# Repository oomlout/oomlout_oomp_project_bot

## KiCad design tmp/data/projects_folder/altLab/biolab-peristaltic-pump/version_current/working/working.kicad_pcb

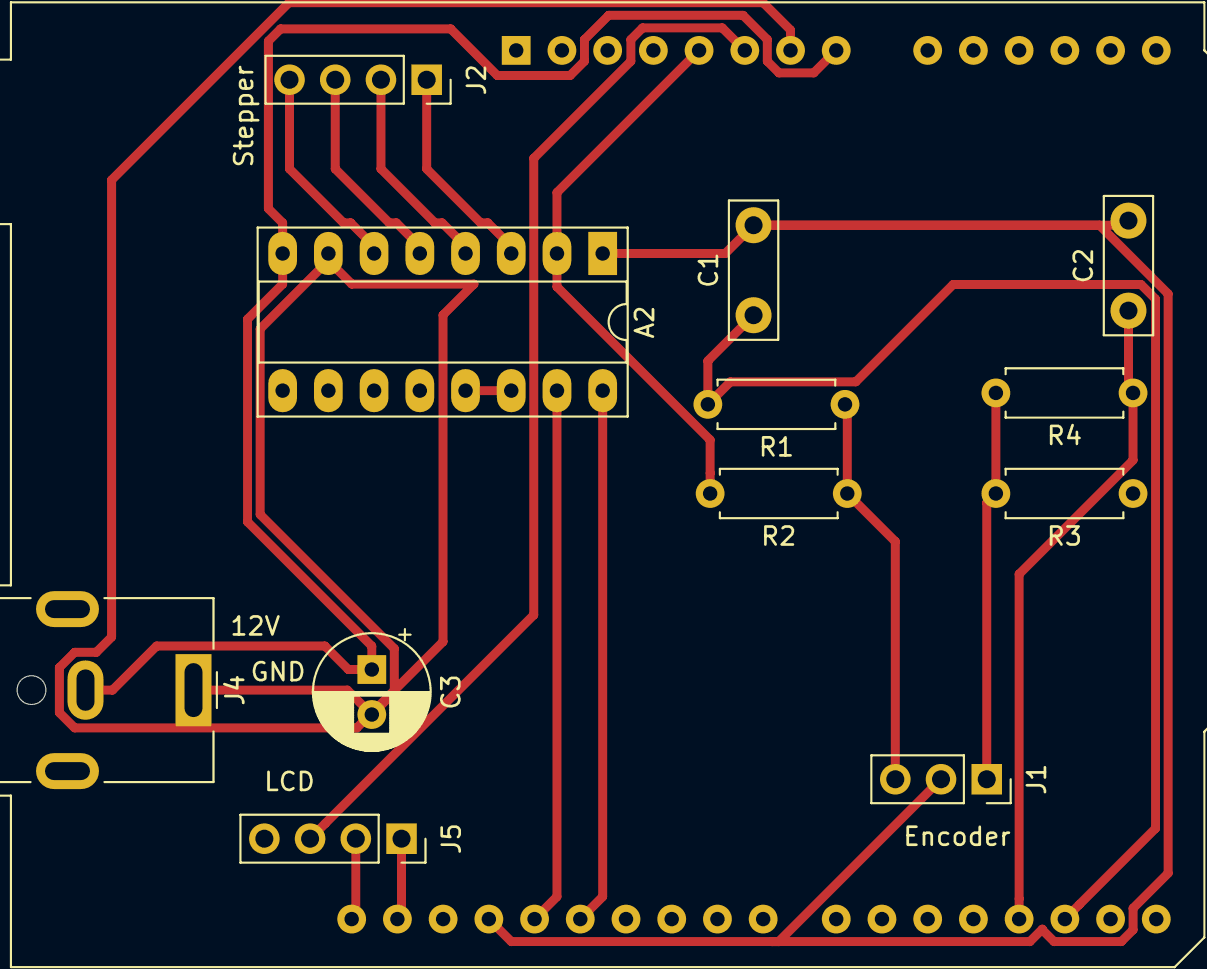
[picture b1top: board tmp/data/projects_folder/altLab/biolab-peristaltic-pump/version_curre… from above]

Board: 2 copper layers, 13 parts (0 on the bottom side), 18 nets.

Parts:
A1: Arduino_UNO_R3
A2: Pololu_Breakout_A4988; DIP-16_W7.62mm_Socket_LongPads
C1, C2: CP; C_Disc_D7.5mm_W2.5mm_P5.00mm
C3: C; CP_Radial_D6.3mm_P2.50mm
J1: Encoder; PinSocket_1x03_P2.54mm_Vertical
J2: Stepper; PinSocket_1x04_P2.54mm_Vertical
J4: Power12V; BarrelJack_CUI_PJ-063AH_Horizontal
J5: LCD-I2C; PinSocket_1x04_P2.54mm_Vertical
R1, R2, R3, R4: R; R_Axial_DIN0207_L6.3mm_D2.5mm_P7.62mm_Horizontal

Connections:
unnamed: A1.5, A2.2, R2.2, R3.1
unnamed: A1.6, J5.3
unnamed: A1.7, A2.7, C3.2, J4.1
unnamed: A1.8, A2.8, C3.1, J4.2
unnamed: A1.17, C1.1, R1.2
unnamed: A1.18, C2.1, R4.1
unnamed: A1.27, A2.16
unnamed: A1.28, A2.15
unnamed: A1.29, A2.1, C1.2, C2.2, J1.2
unnamed: A1.31, J5.1
unnamed: A1.32, J5.2
unnamed: A2.3, J2.1
unnamed: A2.4, J2.2
unnamed: A2.5, J2.3
unnamed: A2.6, J2.4
unnamed: A2.13, A2.14
unnamed: J1.1, R3.2, R4.2
unnamed: J1.3, R1.1, R2.1

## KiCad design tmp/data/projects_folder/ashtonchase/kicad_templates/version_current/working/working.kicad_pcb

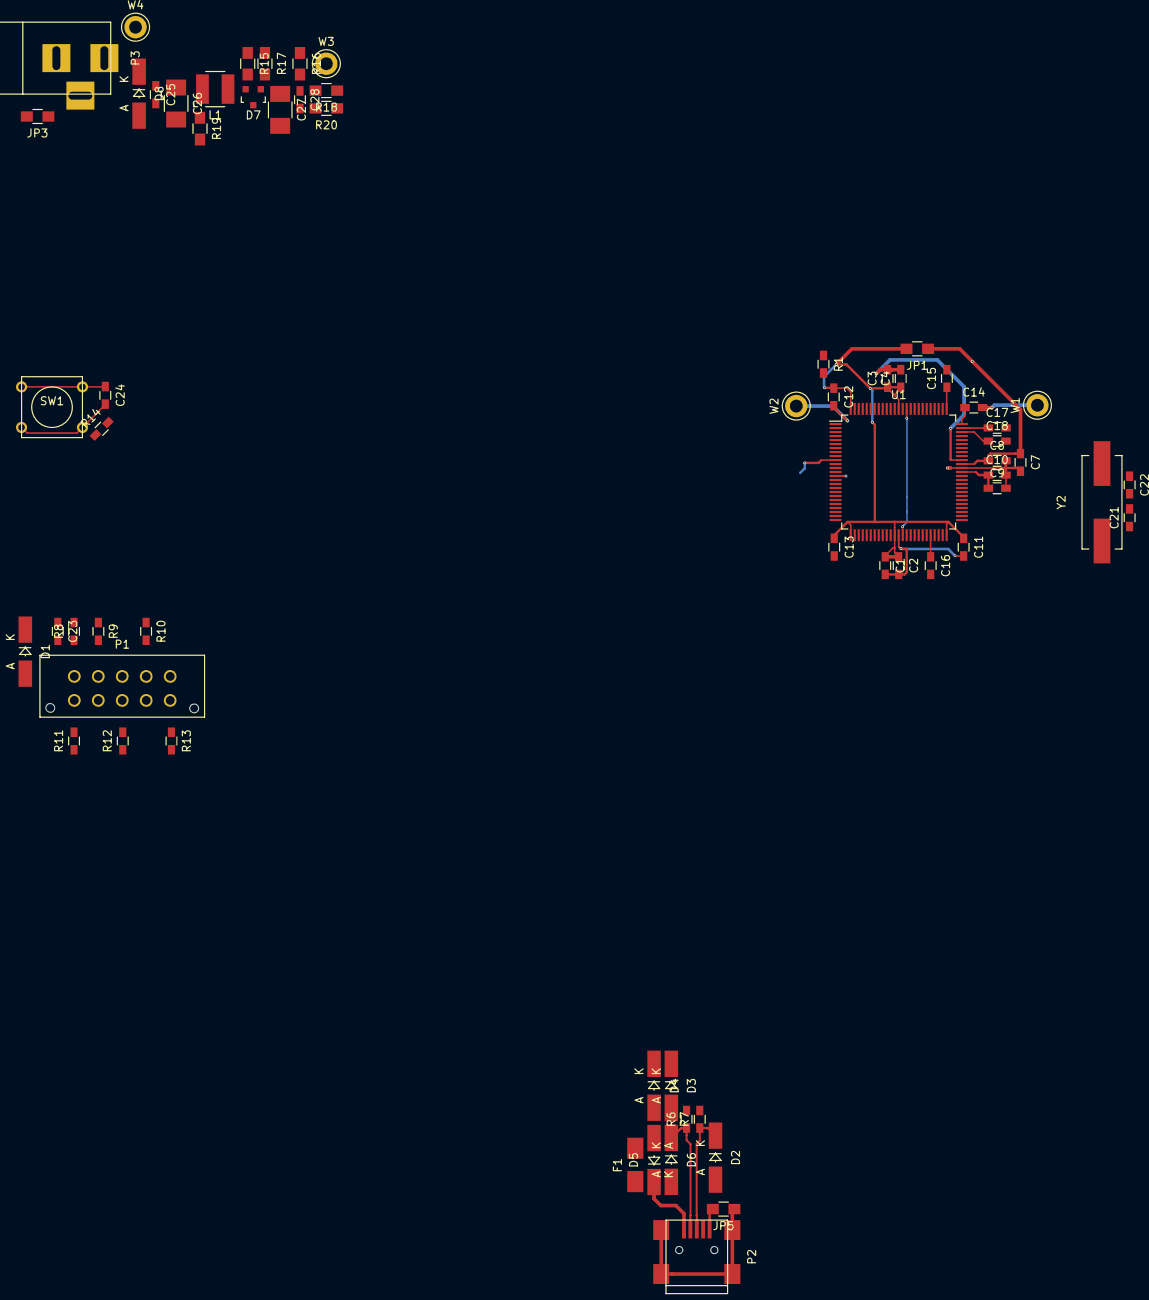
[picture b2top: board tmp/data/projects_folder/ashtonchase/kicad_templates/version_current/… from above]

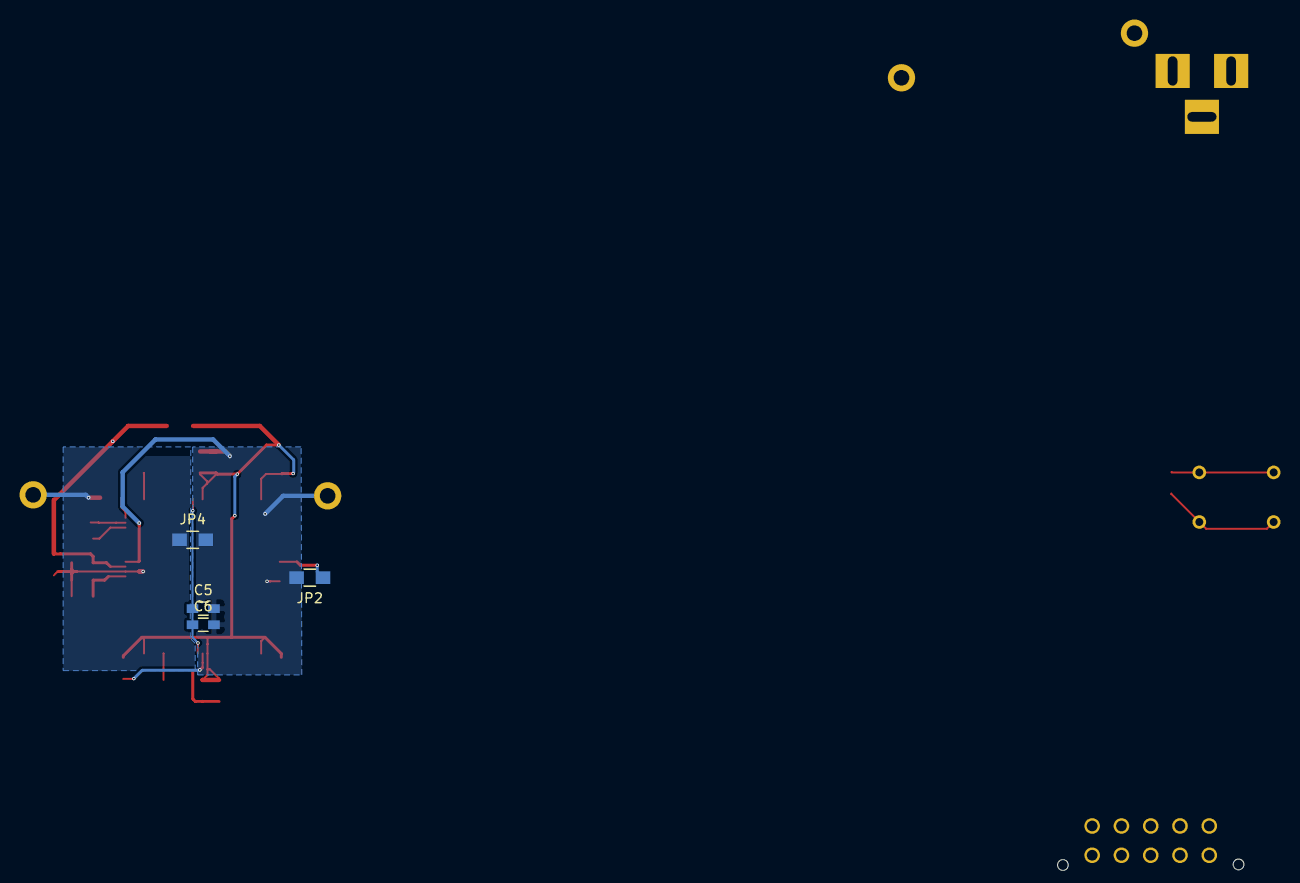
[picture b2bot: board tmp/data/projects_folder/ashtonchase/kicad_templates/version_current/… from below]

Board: 2 copper layers, 67 parts (4 on the bottom side), 39 nets.

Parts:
C1, C3, C5, C7, C9, C15, C16, C17, C18: 1.0UF; R_0603_HandSoldering
C2, C4, C6, C8, C10, C11, C12, C13, C14, C23, C24, C25, C28: 0.1UF; R_0603_HandSoldering
C21, C22: 22PF; R_0603_HandSoldering
C26, C27: 22UF; R_1210_HandSoldering
D1, D2, D5, D6: TVS; MiniMELF_Handsoldering
D3, D4: D_Schottky; MiniMELF_Handsoldering
D7: ZHCS; SOT-23
D8: D; MiniMELF_Handsoldering
F1: FUSE; Fuse_SMD1206_HandSoldering
JP1, JP2, JP3, JP4, JP5: Jumper_NC_Small; R_0805_HandSoldering
L1: 22UH; NR4018
P1: CONN_02X05; Molex_Microfit3_Header_02x05_Straight_43045-1028
P2: USB_OTG; USB_Mini-B
P3: CONN_01X02; BARREL_JACK
R1: 0; R_0603_HandSoldering
R6, R7: 22; R_0603_HandSoldering
R8, R9, R10, R11, R12, R13: 10; R_0603_HandSoldering
R14: 4.7K; R_0603_HandSoldering
R15, R16, R17, R19, R20: NL; R_0805_HandSoldering
R18: 0; R_0805_HandSoldering
SW1: SW_PUSH; SW_PUSH_SMALL
U1: CY8C5888AXI-LP096; LQFP-100_14x14mm_Pitch0.5mm
W1, W2, W3, W4: TEST_1P; Test_Point_Keystone_5010-5014_Multipurpose
Y2: 32.768KHZ; Crystal_HC49-SD_SMD

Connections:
/MCU/P0.2: C18.1, U1.73
/MCU/P0.3: C17.1, U1.74
/MCU/P0.4: C15.1, U1.76
/MCU/P3.2: C16.1, U1.46
/MCU/RTC_N: C22.1, U1.56, Y2.2
/MCU/RTC_P: C21.1, U1.55, Y2.1
/MCU/USBP_N: R6.2, U1.36
/MCU/USBP_P: R7.2, U1.35
/MCU/VCCA: C9.1, C10.1, U1.63
/MCU/VCCD: C5.1, C6.1, U1.39, U1.86
/PSoC Extra Circuits/USB_VCC: D5.1, F1.1, P2.1
Earth: JP5.1, P2.6
GNDA: C7.2, C8.2, C9.2, C10.2, C14.2, C15.2, C16.2, C17.2, C18.2, C21.2, C22.2, JP4.1, U1.64, W1.1
GNDD: C1.2, C2.2, C3.2, C4.2, C5.2, C6.2, C11.2, C12.2, C13.2, C23.2, C24.2, D1.2, D2.2, D5.2, D6.2, JP2.2, JP3.2, JP4.2, JP5.2, P1.3, P1.5, P1.7, P1.9, P2.5, SW1.2, U1.14, U1.38, U1.66, U1.87, W2.1
GNDPWR: JP2.1, U1.10
IND: R15.1, U1.11
unnamed: C27.1, C28.1, D7.1, R16.2, R17.2, R18.2
unnamed: D3.2, D4.2, F1.2
unnamed: D7.2, L1.2, R15.2
unnamed: P1.1, R8.1
unnamed: P1.2, R9.2
unnamed: P1.4, R10.2
unnamed: P1.6, R11.2
unnamed: P1.8, R12.2
unnamed: P1.10, R13.2
P1.0_TMS: R9.1, U1.20
P1.1_TCK: R10.1, U1.21
P1.4_TDO: R11.1, U1.24
P1.5_TDI: R12.1, U1.25
P1.6_nRST: R13.1, U1.27
USB_N: D6.1, P2.2, R6.1
USB_P: D2.1, P2.3, R7.1
VBATT: C25.1, C26.1, D8.1, L1.1, P3.1, R19.1, U1.13, W4.1
VBATT_GND: C25.2, C26.2, C27.2, C28.2, D8.2, JP3.1, P3.2, R19.2, R20.2
VBOOST: R18.1, R20.1, U1.12, W3.1
VDDA: C7.1, C8.1, C14.1, D4.1, JP1.1, R17.1, U1.65, U1.75
VDDD: C1.1, C2.1, C3.1, C4.1, C11.1, C12.1, C13.1, D3.1, JP1.2, R1.1, R16.1, U1.26, U1.37, U1.50, U1.88, U1.100
VTARG: C23.1, D1.1, R1.2, R8.2, R14.1
XRES: C24.1, R14.2, SW1.1, U1.15

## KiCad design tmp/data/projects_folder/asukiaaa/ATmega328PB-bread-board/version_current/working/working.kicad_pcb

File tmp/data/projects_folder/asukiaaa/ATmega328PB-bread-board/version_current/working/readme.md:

# ATmega328PB-bread-board by asukiaaa  
This is a harvested standardized copy of a project from github.  
The original project can be found at:  
https://github.com/asukiaaa/ATmega328PB-bread-board  
Please consult that link for additional, details, files, and license information.  
Note: It was auto harvested and if the original repo had more than one board file or anything out of the ordinary the files here are likely not representative.

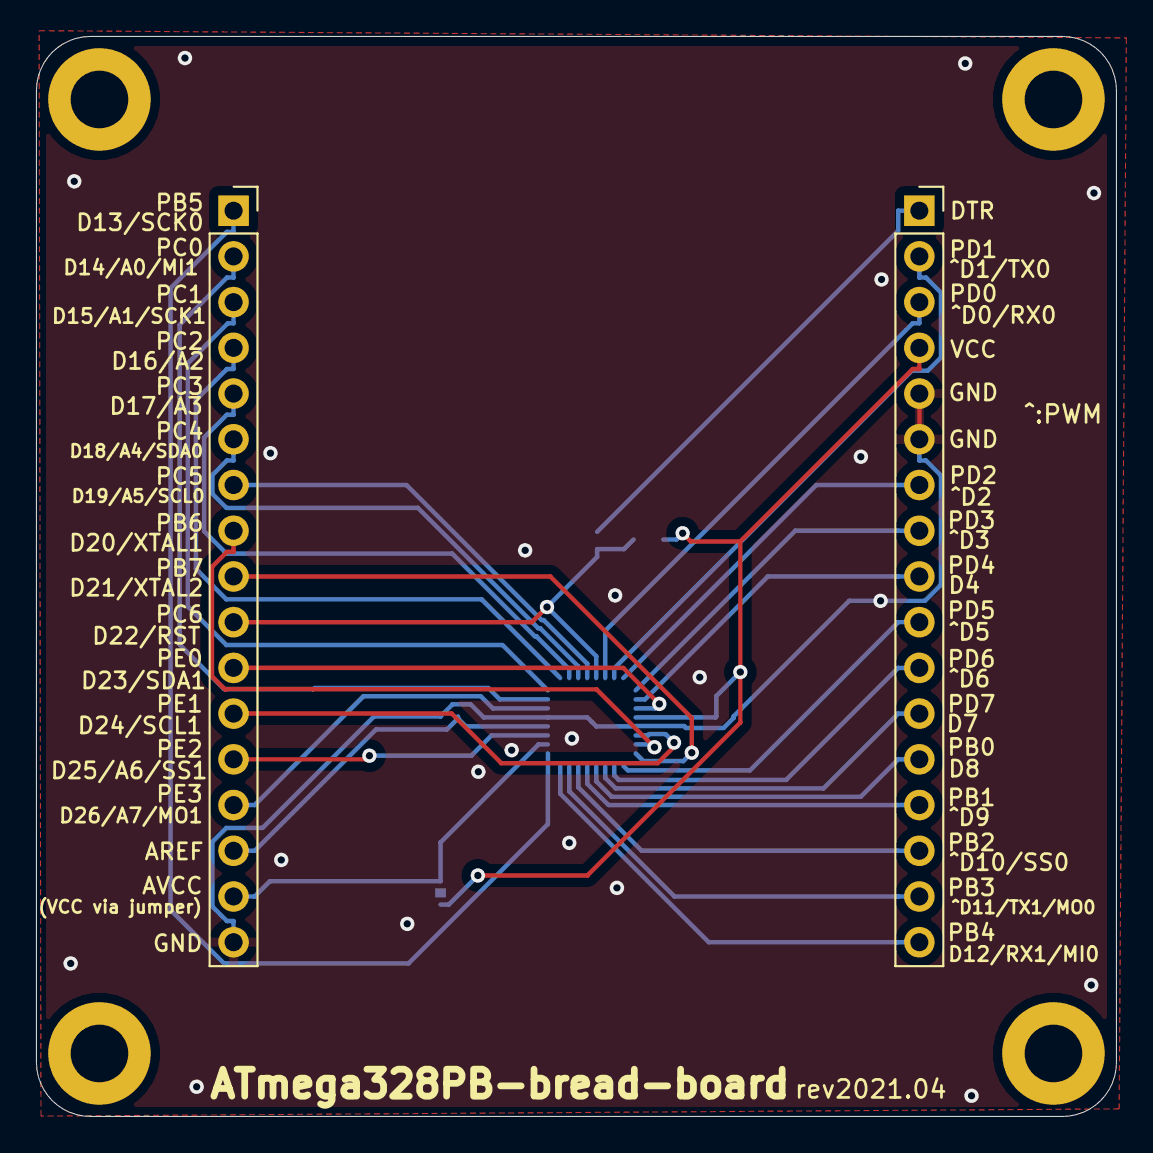
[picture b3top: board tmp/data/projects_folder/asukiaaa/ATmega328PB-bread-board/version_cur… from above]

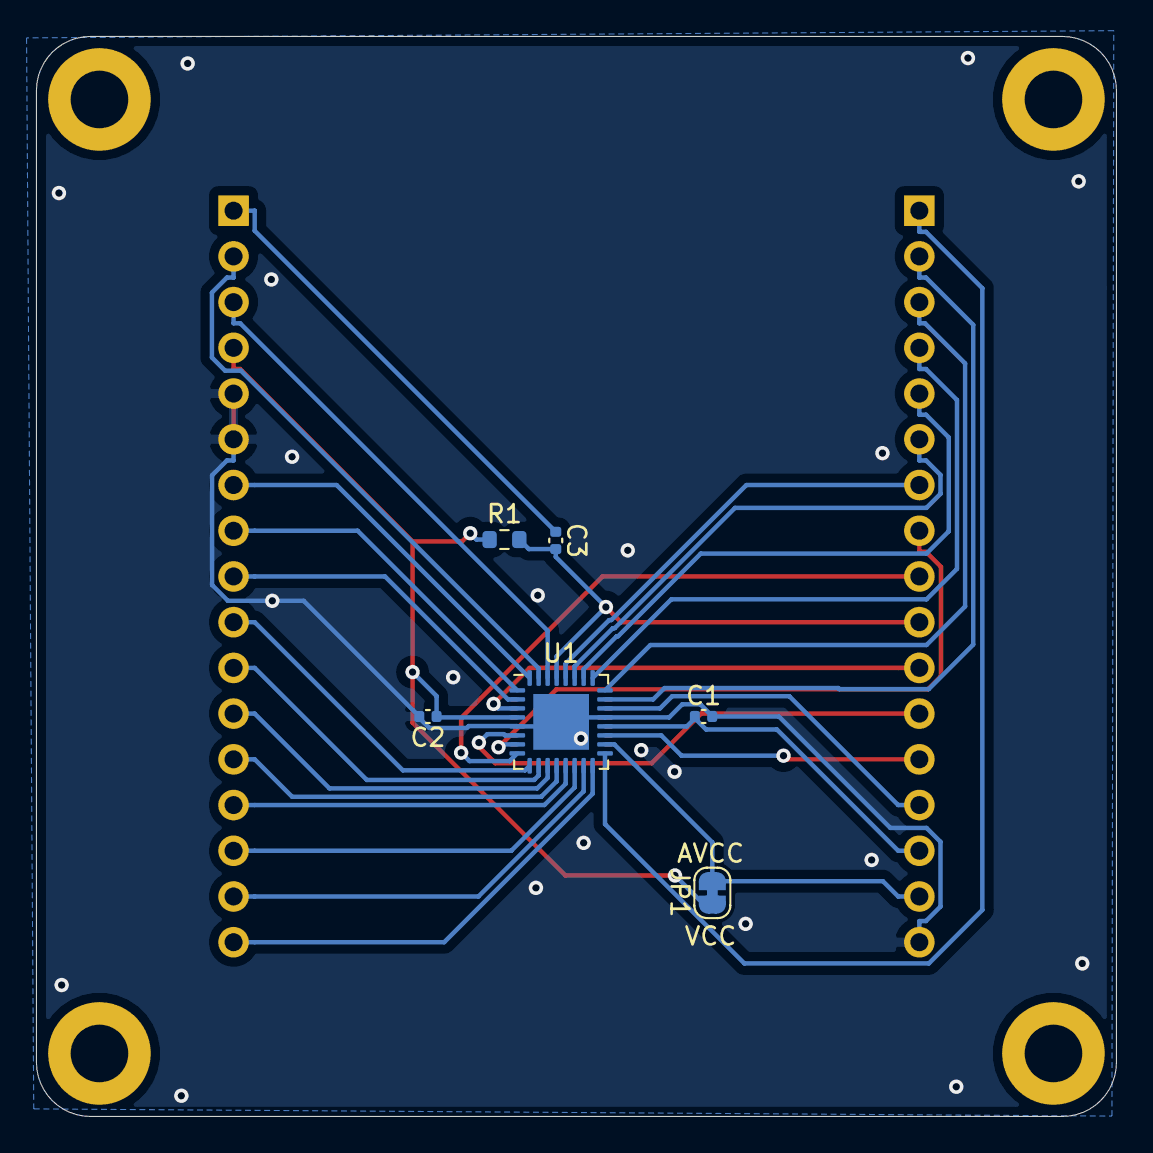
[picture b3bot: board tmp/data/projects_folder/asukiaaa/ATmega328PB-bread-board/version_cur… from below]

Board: 2 copper layers, 60.0 x 60.0 mm, 12 parts (6 on the bottom side), 32 nets.

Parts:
C1, C2, C3: 0.1uf; C_0402_1005Metric
J1, J2: Conn_01x17; PinSocket_1x17_P2.54mm_Vertical
JP1: NC; SolderJumper-2_P1.3mm_Bridged_RoundedPad1.0x1.5mm
R1: 10k; R_0603_1608Metric
REF1, REF2, REF3, REF4: MountingHole_3.2mm_M3_ISO7380_Pad
U1: ATmega328PB-MU; QFN-32-1EP_5x5mm_P0.5mm_EP3.1x3.1mm

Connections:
/DTR: C3.1, J1.1
/aref: C1.1, J2.15, U1.20
/avcc: J2.16, JP1.2, U1.18
/pb0: J1.13, U1.12
/pb1: J1.14, U1.13
/pb2: J1.15, U1.14
/pb3: J1.16, U1.15
/pb4: J1.17, U1.16
/pb5: J2.1, U1.17
/pb6: J2.8, U1.7
/pb7: J2.9, U1.8
/pc0: J2.2, U1.23
/pc1: J2.3, U1.24
/pc2: J2.4, U1.25
/pc3: J2.5, U1.26
/pc4: J2.6, U1.27
/pc5: J2.7, U1.28
/pc6: C3.2, J2.10, R1.2, U1.29
/pd0: J1.3, U1.30
/pd1: J1.2, U1.31
/pd2: J1.7, U1.32
/pd3: J1.8, U1.1
/pd4: J1.9, U1.2
/pd5: J1.10, U1.9
/pd6: J1.11, U1.10
/pd7: J1.12, U1.11
/pe0: J2.11, U1.3
/pe1: J2.12, U1.6
/pe2: J2.13, U1.19
/pe3: J2.14, U1.22
GND: C1.2, C2.2, J1.5, J1.6, J2.17, U1.5, U1.21, U1.33
VCC: C2.1, J1.4, JP1.1, R1.1, U1.4

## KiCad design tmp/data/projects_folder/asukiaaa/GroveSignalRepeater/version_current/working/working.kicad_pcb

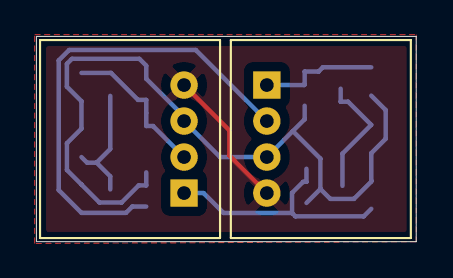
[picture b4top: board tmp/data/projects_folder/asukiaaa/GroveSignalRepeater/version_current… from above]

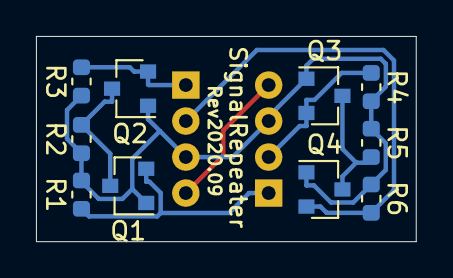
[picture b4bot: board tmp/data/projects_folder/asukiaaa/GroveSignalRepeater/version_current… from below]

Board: 2 copper layers, 21.1 x 11.4 mm, 12 parts (10 on the bottom side), 8 nets.

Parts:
J1, J2: Conn_01x04; NS-Tech_Grove_1x04_P2mm_Horizontal
Q1, Q2, Q3, Q4: Q_NMOS_GSD; SOT-23
R1, R2, R3, R4, R5, R6: 10k; R_0603_1608Metric

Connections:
/CON1_A: J1.1, Q1.2, R1.1
/CON1_B: J1.2, Q3.2, R4.1
/CON2_A: J2.1, Q2.2, R3.2
/CON2_B: J2.2, Q4.2, R6.2
GND: J1.4, J2.4
unnamed: Q1.3, Q2.3, R2.2
unnamed: Q3.3, Q4.3, R5.2
VCC: J1.3, J2.3, Q1.1, Q2.1, Q3.1, Q4.1, R1.2, R2.1, R3.1, R4.2, R5.1, R6.1

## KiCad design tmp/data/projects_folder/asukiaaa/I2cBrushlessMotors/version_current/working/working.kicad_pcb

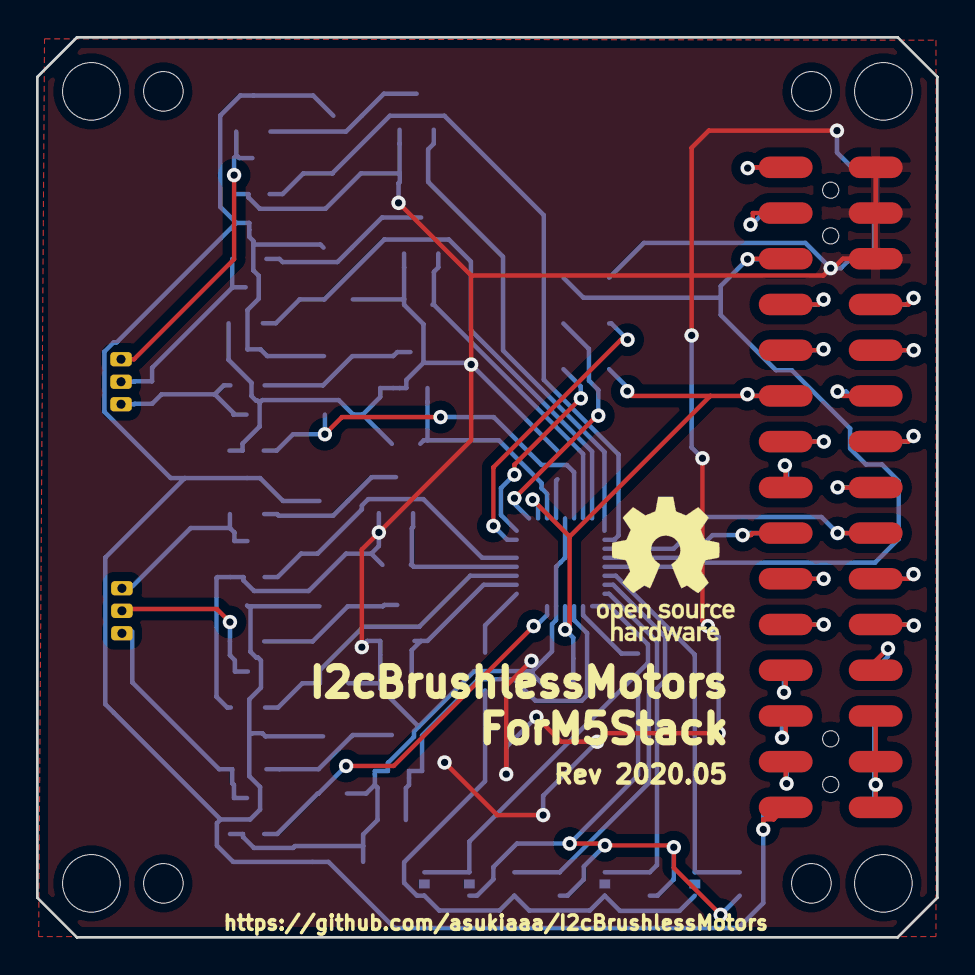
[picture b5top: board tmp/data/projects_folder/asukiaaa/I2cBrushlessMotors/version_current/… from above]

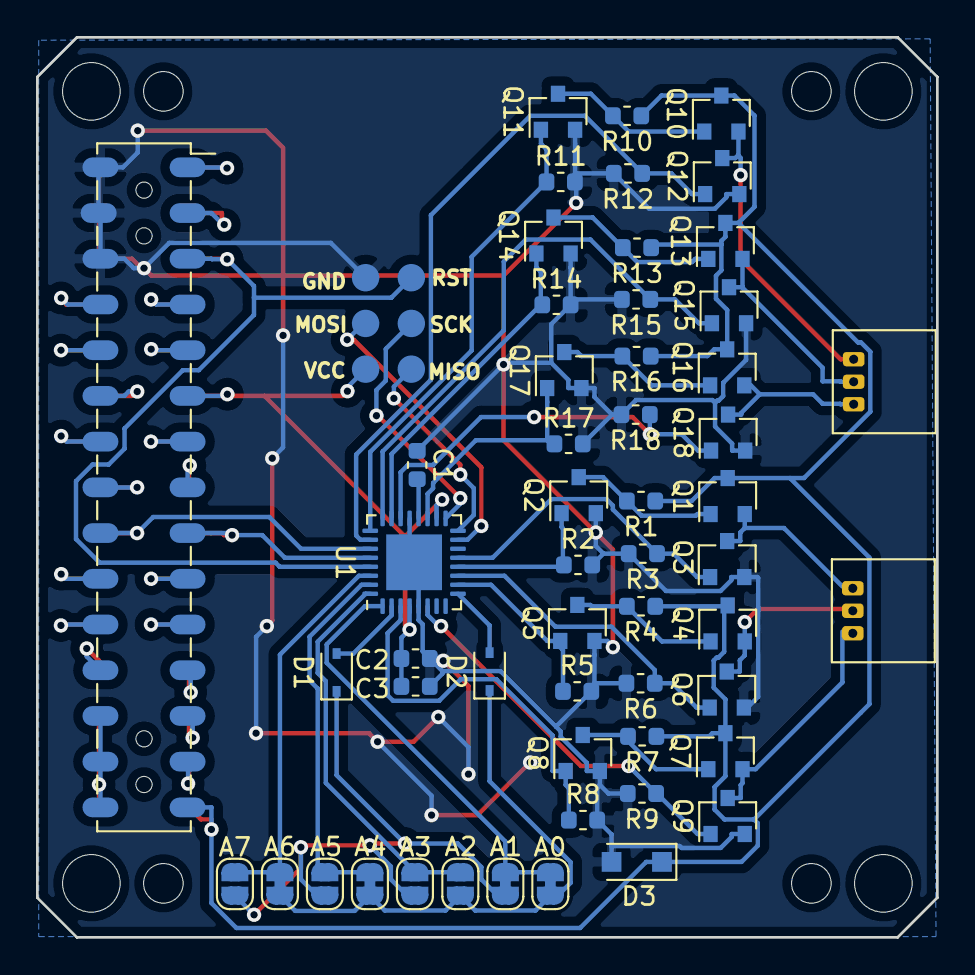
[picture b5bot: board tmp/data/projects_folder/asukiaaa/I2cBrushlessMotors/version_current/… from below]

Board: 2 copper layers, 50.0 x 50.0 mm, 64 parts (55 on the bottom side), 62 nets.

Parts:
A0, A1, A4, A6: NC; SolderJumper-2_P1.3mm_Bridged_RoundedPad1.0x1.5mm
A2, A3, A5, A7: NO; SolderJumper-2_P1.3mm_Open_RoundedPad1.0x1.5mm
C1, C3: 0.1uf; C_0603_1608Metric
C2: 1uf; C_0603_1608Metric
D1, D2: D; D_SOD-323
D3: D; D_SOD-123F
J1, J5: Conn_01x03; Molex_1x03_P1.25mm_Vertical
J2: Conn_01x06; 2x03_P2.54mm_Pads
J3: Header; PinHeader_2x15_P2.54mm_M5Stack
J4: Socket; PinSocket_2x15_P2.54mm_Vertical_SMD_just_for_M5Stack_bottom
Q1, Q4, Q7, Q10, Q13, Q16: Q_PMOS_GSD; SOT-23
Q2, Q3, Q5, Q6, Q8, Q9, Q11, Q12, Q14, Q15, Q17, Q18: Q_NMOS_GSD; SOT-23
R1, R2, R3, R4, R5, R6, R7, R8, R9, R10, R11, R12, R13, R14, R15, R16, R17, R18: 10k; R_0603_1608Metric
REF1, REF4, REF6, REF9: MountingHole_3.2mm_M3
REF2, REF3, REF7, REF8: MountingHole_2.2mm_M2
U1: ATmega328PB-MU; QFN-32-1EP_5x5mm_P0.5mm_EP3.1x3.1mm

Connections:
+3V3: C2.2, C3.2, J2.2, J3.11, J4.11, U1.4, U1.18
+5V: J3.27, J4.27
+BATT: D3.1, J3.29, J4.29, Q1.3, Q4.3, Q7.3, Q10.3, Q13.3, Q16.3, R1.1, R4.1, R7.1, R10.1, R13.1, R16.1
/0: J3.23, J4.23
/1: J3.13, J4.13
/2: J3.20, J4.20
/3: J3.14, J4.14
/5: J3.19, J4.19
/12: J3.22, J4.22
/13: J3.21, J4.21
/15: J3.24, J4.24
/16: J3.16, J4.16
/17: J3.15, J4.15
/18: J3.12, J4.12
/19: J3.10, J4.10
/21_SDA: J3.18, J4.18, U1.27
/22_SCL: J3.17, J4.17, U1.28
/23: J3.8, J4.8
/25: J3.7, J4.7
/26: J3.9, J4.9
/34: J3.25, J4.25
/35: J3.1, J4.1
/36: J3.3, J4.3
/A01: A0.1, A1.1, U1.1
/A23: A2.1, A3.1, U1.32
/A45: A4.1, A5.1, U1.31
/A67: A6.1, A7.1, U1.30
/HPWR: J3.26, J3.28, J3.30, J4.26, J4.28, J4.30
/M1A: J1.1, Q1.2, Q3.3
/M1AH: Q2.1, R2.1, U1.12
/M1AL: Q3.1, R3.1, U1.13
/M1B: J1.2, Q4.2, Q6.3
/M1BH: Q5.1, R5.1, U1.10
/M1BL: Q6.1, R6.1, U1.11
/M1C: J1.3, Q7.2, Q9.3
/M1CH: Q8.1, R8.1, U1.3
/M1CL: Q9.1, R9.1, U1.6
/M2A: J5.1, Q10.2, Q12.3
/M2AH: Q11.1, R11.1, U1.25
/M2AL: Q12.1, R12.1, U1.26
/M2B: J5.2, Q13.2, Q15.3
/M2BH: Q14.1, R14.1, U1.23
/M2BL: Q15.1, R15.1, U1.24
/M2C: J5.3, Q16.2, Q18.3
/M2CH: Q17.1, R17.1, U1.19
/M2CL: Q18.1, R18.1, U1.22
/MISO: J2.1, U1.16
/MOSI: J2.4, U1.15
/RST: J2.5, J3.5, J4.5, U1.29
/SCK: J2.3, U1.17
GND: C1.1, C2.1, C3.1, D3.2, J2.6, J3.2, J3.4, J3.6, J4.2, J4.4, J4.6, Q2.2, Q3.2, Q5.2, Q6.2, Q8.2, Q9.2, Q11.2, Q12.2, Q14.2, Q15.2, Q17.2, Q18.2, R2.2, R3.2, R5.2, R6.2, R8.2, R9.2, R11.2, R12.2, R14.2, R15.2, R17.2, R18.2, U1.5, U1.21, U1.33
unnamed: A0.2, A2.2, A4.2, A6.2, D2.1
unnamed: A1.2, A3.2, A5.2, A7.2, D1.1
unnamed: C1.2, U1.20
unnamed: D1.2, U1.2
unnamed: D2.2, U1.9
unnamed: Q1.1, Q2.3, R1.2
unnamed: Q4.1, Q5.3, R4.2
unnamed: Q7.1, Q8.3, R7.2
unnamed: Q10.1, Q11.3, R10.2
unnamed: Q13.1, Q14.3, R13.2
unnamed: Q16.1, Q17.3, R16.2

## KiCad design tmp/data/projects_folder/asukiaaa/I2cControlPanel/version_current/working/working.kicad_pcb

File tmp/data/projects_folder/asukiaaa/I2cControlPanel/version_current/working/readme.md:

# I2cControlPanel by asukiaaa  
This is a harvested standardized copy of a project from github.  
The original project can be found at:  
https://github.com/asukiaaa/I2cControlPanel  
Please consult that link for additional, details, files, and license information.  
Note: It was auto harvested and if the original repo had more than one board file or anything out of the ordinary the files here are likely not representative.

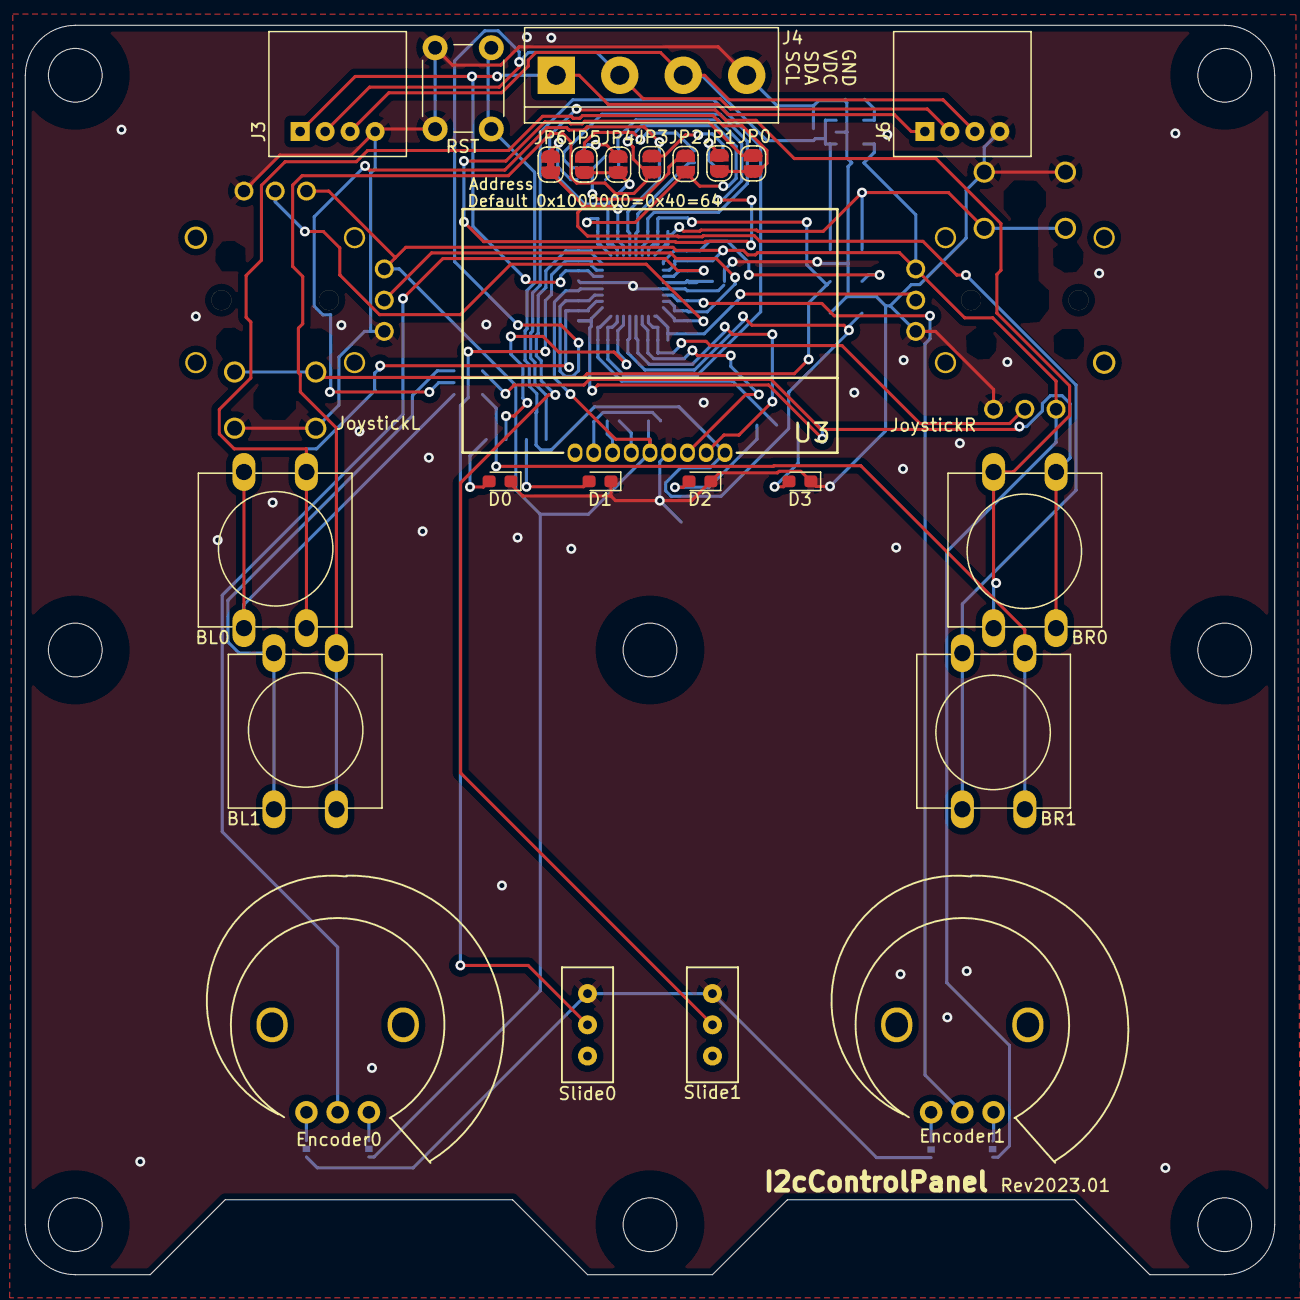
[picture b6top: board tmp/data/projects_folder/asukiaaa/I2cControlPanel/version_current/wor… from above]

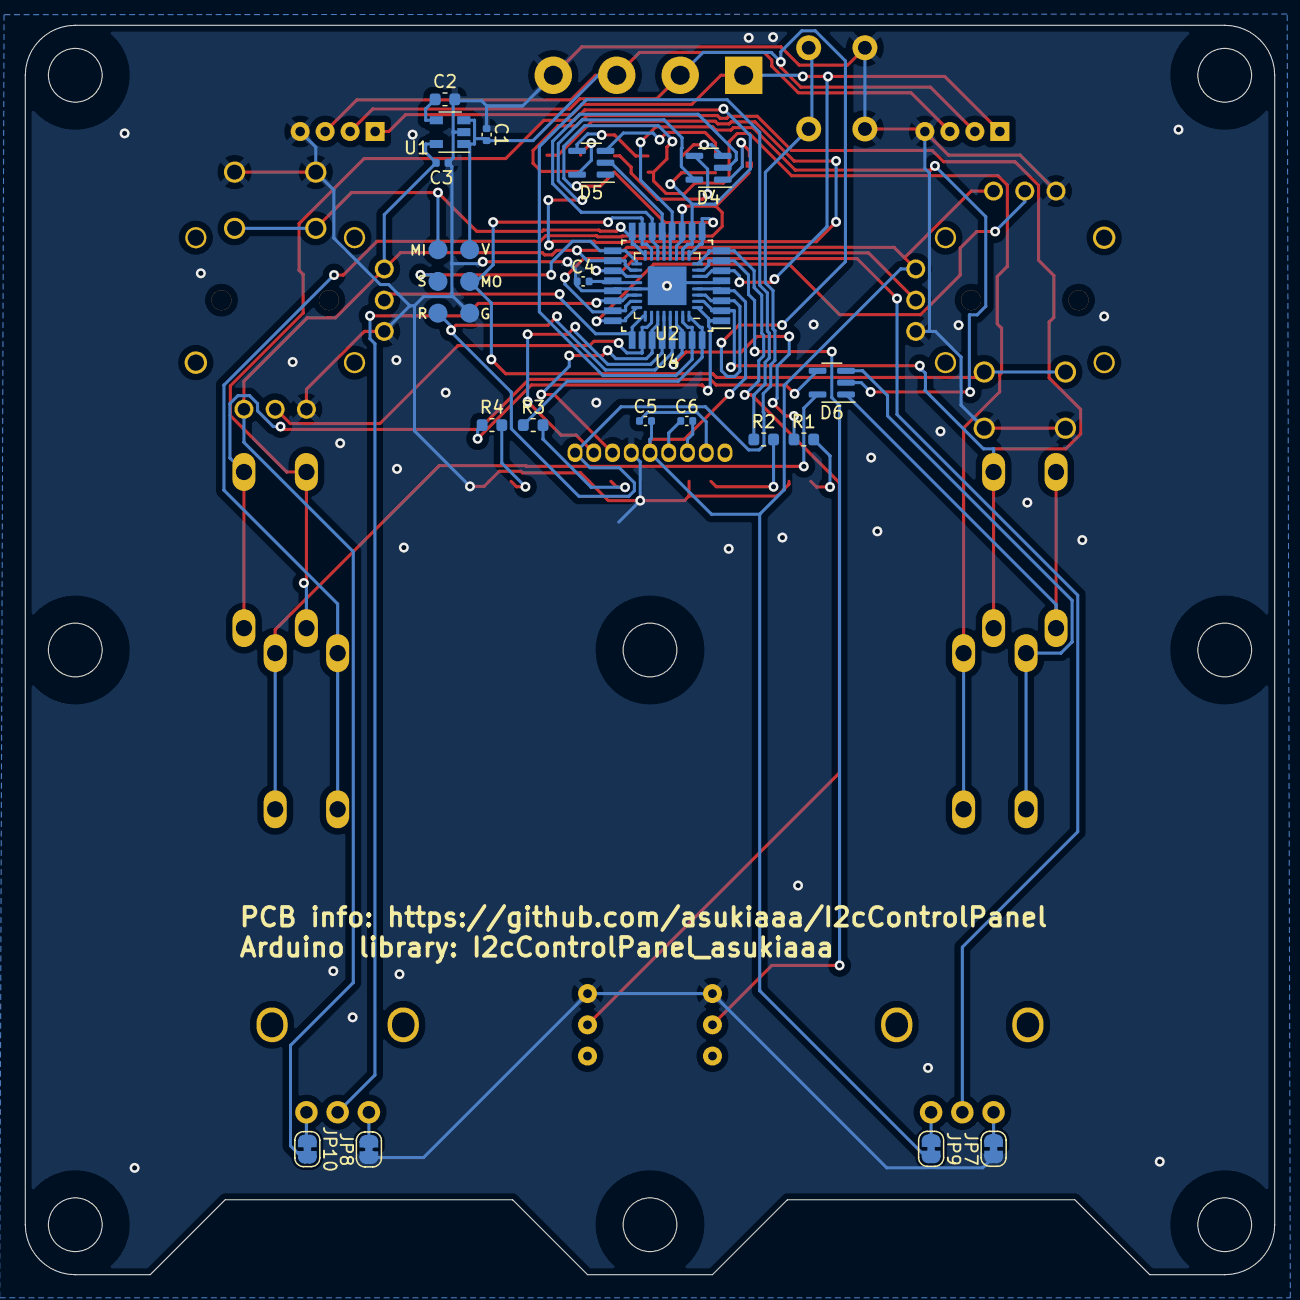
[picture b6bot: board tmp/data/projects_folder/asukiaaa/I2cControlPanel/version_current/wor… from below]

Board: 2 copper layers, 100.0 x 100.0 mm, 55 parts (21 on the bottom side), 54 nets.

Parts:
BL0, BL1: SW_Push; SW_Center_PUSH-12mm
BR0, BR1: SW_Push; SW_Center_PUSH-12mm
C1, C4, C5, C6: 0.1u; C_0402_1005Metric
C2: 10n; C_0603_1608Metric
C3: 0.47u; C_0402_1005Metric
D0: LED0; D_0603_1608Metric_Pad1.05x0.95mm_HandSolder
D1: LED1; D_0603_1608Metric_Pad1.05x0.95mm_HandSolder
D2: LED2; D_0603_1608Metric_Pad1.05x0.95mm_HandSolder
D3: LED3; D_0603_1608Metric_Pad1.05x0.95mm_HandSolder
D4, D5, D6: 1SS309; SC-74-5_1.6x2.9mm_P0.95mm
Encoder0, Encoder1: R_POT_US; RoteryEncoderWithPowerLabel
J1: JoystickL; PS4tJoystick
J2: Conn_01x06; 2x03_P2.54mm_Pads
J3, J6: Conn_01x04; NS-Tech_Grove_1x04_P2mm_Horizontal
J4: Conn_01x04; TerminalBlock_bornier-4_P5.08mm
J5: JoystickR; PS4tJoystick
JP0, JP1, JP2, JP3, JP4, JP5: NO; SolderJumper-2_P1.3mm_Open_RoundedPad1.0x1.5mm
JP6, JP7, JP8, JP9, JP10: NC; SolderJumper-2_P1.3mm_Bridged_RoundedPad1.0x1.5mm
R1, R2, R3, R4: 10k; R_0603_1608Metric
REF1, REF2, REF3, REF4, REF5, REF6, REF7, REF8: MountingHole_4.3mm_M4_bare
SW6: SW_Push; SW_PUSH_6mm
Slide0, Slide1: SlideSwitch; SlideSwitch_SS12D01G4_2posi_1line
U1: NJM12888F33; SOT-23-5
U2: ATmega328PB-MU; QFN-32-1EP_5x5mm_P0.5mm_EP3.1x3.1mm
U3: AQM0802; AQM0802A-RN-GBW
U4: ATmega328PB-A; TQFP-32_7x7mm_P0.8mm_short_inner

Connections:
+3V3: C3.1, C5.2, J1.3, J1.4, J5.1, J5.6, JP9.2, JP10.2, U1.5 (Vout), U2.4 (VCC), U2.18 (AVCC), U3.5 (VDD), U4.4 (VCC), U4.18 (AVCC)
/BTN0: BL0.2, JP0.1, JP1.1, U2.2 (PD4), U4.2 (PD4)
/BTN1: BL1.2, JP2.1, JP3.1, U2.9 (PD5), U4.9 (PD5)
/BTN2: BR0.2, JP4.1, JP5.1, U2.10 (PD6), U4.10 (PD6)
/BTN3: BR1.2, JP6.1, U2.11 (PD7), U4.11 (PD7)
/BtnSig0: D6.2, U2.12 (PB0), U4.12 (PB0)
/BtnSig1: D5.2, U2.13 (PB1), U4.13 (PB1)
/BtnSig2: D4.2, U2.14 (PB2), U4.14 (PB2)
/HoriValueL: J1.2, U2.24 (PC1), U4.24 (PC1)
/HoriValueR: J5.2, U2.26 (PC3), U4.26 (PC3)
/JoyBtnL: J1.7, J2.4, U2.15 (PB3), U4.15 (PB3)
/JoyBtnR: J2.1, J5.7, U2.16 (PB4), U4.16 (PB4)
/LED0: R1.1, U2.30 (PD0), U4.30 (PD0)
/LED1: R2.1, U2.31 (PD1), U4.31 (PD1)
/LED2: R3.1, U2.32 (PD2), U4.32 (PD2)
/LED3: R4.1, U2.1 (PD3), U4.1 (PD3)
/RST: J2.5, SW6.1, U2.29 (~RESET/PC6), U3.9 (XRSETB), U4.29 (~RESET/PC6)
/Rotery1: Encoder0.2, U2.19 (PE2), U4.19 (PE2)
/Rotery2: Encoder1.2, U2.22 (PE3), U4.22 (PE3)
/SCK: J2.3, U2.17 (PB5), U4.17 (PB5)
/SCL: J3.1, J4.1, J6.1, U2.6 (PE1), U4.6 (PE1)
/SCL_inside: U2.28 (PC5), U3.8 (SCL), U4.28 (PC5)
/SDA: J3.2, J4.2, J6.2, U2.3 (PE0), U4.3 (PE0)
/SDA_inside: U2.27 (PC4), U3.7 (SDA), U4.27 (PC4)
/Slide0: Slide0.2 (B), U2.7 (XTAL1/PB6), U4.7 (XTAL1/PB6)
/Slide1: Slide1.2 (B), U2.8 (XTAL2/PB7), U4.8 (XTAL2/PB7)
/VertValueL: J1.5, U2.23 (PC0), U4.23 (PC0)
/VertValueR: J5.5, U2.25 (PC2), U4.25 (PC2)
GND: C1.2, C2.2, C3.2, C4.1, D0.1 (K), D1.1 (K), D2.1 (K), D3.1 (K), J1.1, J1.6, J1.8, J2.6, J3.4, J4.4, J5.3, J5.4, J5.8, J6.4, JP7.1, JP8.1, SW6.2, Slide0.1 (A), Slide1.1 (A), U1.2 (GND), U2.5 (GND), U2.21 (GND), U2.33 (GND), U3.6 (VSS), U4.5 (GND), U4.21 (GND)
unnamed: BL0.1, D6.1
unnamed: BL1.1, D6.3
unnamed: BR0.1, D6.4
unnamed: BR1.1, D6.5
unnamed: C2.1, U1.4 (CS)
unnamed: C4.2, U2.20 (AREF), U4.20 (AREF)
unnamed: C5.1, U3.2 (VOUT)
unnamed: C6.1, U3.4 (CAP1P)
unnamed: C6.2, U3.3 (CAP1N)
unnamed: D0.2 (A), R1.2
unnamed: D1.2 (A), R2.2
unnamed: D2.2 (A), R3.2
unnamed: D3.2 (A), R4.2
unnamed: D4.1, JP6.2
unnamed: D4.3, JP4.2
unnamed: D4.4, JP2.2
unnamed: D4.5, JP0.2
unnamed: D5.3, JP5.2
unnamed: D5.4, JP3.2
unnamed: D5.5, JP1.2
unnamed: Encoder0.1, JP7.2
unnamed: Encoder0.3, JP9.1
unnamed: Encoder1.1, JP8.2
unnamed: Encoder1.3, JP10.1
VDC: C1.1, J2.2, J3.3, J4.3, J6.3, U1.1 (VIN), U1.3 (CTL)
